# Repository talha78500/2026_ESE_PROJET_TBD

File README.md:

# 2026_ESE_PROJET_TBD

## Procédure de test de la carte

### Tests d'alimentation

La 1ère étape pour tester le pcb est de souder les solder bridges. Une fois les soudures faites, une alimentation de laboratoire est utilisée pour alimenter la carte. Pour ne pas endommager la carte en cas de court circuit, le courant de l'alimentation est limité à 100mA. On peut ensuite venir tester un à un les différents points de test de la carte. Les différents points de test sont relié au 5v, 3v3, sys et GND. Lors des des tests d'alimentation, des led temoigneront du fonctionnement : 

<div align="center">

</div>

| Test point alimenté | LED Temoin | LED allumée(s) en conséquence |Explication |
| :--- | :--- | :--- | :--- |
| 3v3 | Led rouge D1| X |X |
| 5v  | Led verte D2 | Led verte D2 orange D3 et rouge D4 | Le 5v alimente le régulateur 3v3 donc la led D2 s'allume. |
| SYS | Led rouge D4| X |X |

### Test du chargeur

Avant d'utiliser la batterie, les premiers essais du chargeur sont réalisés avec une alimentation 3v8 1A. Il faut programmer le chargeur via I2C: 
- Désactiver le timer interne (REG07, bits 5:4 = 00)
- Configurer la tension de sortie  boostée (REG0A)
- Couper la charge (REG03) (CHG_CONFIG = 0->Bit 4)
- Activer la sortie boostée (REG03) (OTG_CONFIG = 1 ->Bit 5)

Une fois tout cette partie validée, la batterie peut être branchée.

### Test du fuel gauge 

---

## Mise à jour OTA (PC → BLE → nRF52840 → UART → STM32G431)

### 1. Contexte et architecture

Le PCB ne donnant pas accès aux broches `NRST` et `BOOT0` de la STM32G431RBT6 depuis le nRF52840 (`nice!nano`), la reprogrammation passe exclusivement par la liaison UART reliant les deux microcontrôleurs :

| Signal | STM32G431RBT6 (`USART3`) | nRF52840 `nice!nano` (`uart0`) | Paramètres |
| :--- | :--- | :--- | :--- |
| TX → RX | `PC10` (`USART3_TX`) | `P0.08` (`UART_RX`, pull-up) | `115200` bauds, `8N1` |
| RX ← TX | `PC11` (`USART3_RX`) | `P0.06` (`UART_TX`) | Sans contrôle de flux |

Le nRF52840 ne disposant pas de contrôleur Wi-Fi intégré, la réception sans fil du firmware depuis le PC s'effectue en **Bluetooth Low Energy (BLE)** via une interface Web Bluetooth locale en glisser-déposer.

```text
PC (Chrome/Edge : stm32_ble_ota.html)
        │  BLE GATT ("Robot_STM32_OTA", paquets MTU jusqu'à 244 o)
        ▼
nRF52840 (Zephyr / NCS v2.9.3 : tampon RAM 112 Ko + contrôle CRC32)
        │  UART 115200 8N1 (P0.06 TX / P0.08 RX)
        ▼
STM32G431 (Bootloader permanent 0x08000000 → Flash App 0x08004000)
```

---

### 2. Cartographie mémoire STM32G431RBT6

La Flash interne (`128 Ko`, `64` pages de `2 Ko`, banque unique) et la SRAM (`32 Ko`) sont partitionnées ainsi :

| Zone | Plage d'adresses | Taille | Rôle |
| :--- | :--- | :--- | :--- |
| **Bootloader permanent** | `0x08000000` – `0x08003FFF` | `16 Ko` (pages 0..7) | Reçoit le firmware sur `USART3`, écrit la Flash App et saute vers l'application |
| **Application Robot** | `0x08004000` – `0x0801FFFF` | `112 Ko` (pages 8..63) | Firmware robot FreeRTOS (`SCB->VTOR = 0x08004000`) avec écoute OTA active |
| **SRAM applicative** | `0x20000000` – `0x20007FEF` | `32 Ko - 16 o` | Pile, heap et variables (`_estack = 0x20007FF0`) |
| **Mailbox OTA SRAM** | `0x20007FF0` – `0x20007FFF` | `16 octets` | Drapeau `0xB00710AD` posé avant `NVIC_SystemReset()` pour forcer l'entrée en bootloader |

---

### 3. Protocole série OTA et mécanisme de mise à jour

- **Format de trame (`Informatics/ota/ota_protocol.h`) :**
  `[0xAA, 0x55, CMD, LEN_LE (2 o), PAYLOAD (0..260 o), CRC32_LE (4 o)]` (CRC-32 IEEE 802.3).
  Réponses STM32 fixes sur `4` octets : `[0xAA, 0x55, RSP, ERR]` (`ACK=0x79`, `NACK=0x1F`, `READY=0x5A`, `REBOOTING=0x55`).
- **Auto-hébergement des mises à jour futures :**
  Chaque firmware applicatif initialise `ota_init(&huart3)` et appelle `ota_process()` dans la boucle FreeRTOS (`Core/Src/app_freertos.c`). Lorsqu'une trame `OTA_CMD_SYNC` (ou `"$$OTA$$"`, ou la commande shell `ota`) arrive :
  1. L'application coupe les moteurs (`motor_stop_all()`), répond `OTA_RSP_REBOOTING`, écrit `0xB00710AD` dans la mailbox SRAM et déclenche `NVIC_SystemReset()`.
  2. Le bootloader démarre, détecte la mailbox, efface `0` et répond `OTA_RSP_READY`. *(Au boot normal sans mailbox, il attend `350 ms` un `SYNC` éventuel avant de sauter vers l'app valide.)*
  3. **`OTA_CMD_BEGIN`** : transmet la taille totale et le CRC32 ; le bootloader efface uniquement les pages applicatives nécessaires (`>= page 8`).
  4. **`OTA_CMD_DATA`** : transfère le `.bin` par blocs de `256` octets max (écriture double-word `64 bits`, retry idempotent jusqu'à `3` tentatives).
  5. **`OTA_CMD_END`** : recalcule le CRC32 sur toute la zone écrite, vérifie le vecteur `MSP`/`Reset_Handler` à `0x08004000`, puis exécute `jump_to_app()`.
- **Cohabitation avec les `printf` :** `_write()` envoie aussi les sorties texte sur `USART3`. Le décodeur côté nRF52840 ignore les octets hors trame `[0xAA, 0x55, ...]` pendant l'OTA et relaie les lignes `[STM32] ...` sur la console USB de la `nice!nano` au repos.

---

### 4. Inventaire des fichiers ajoutés et modifiés

#### Côté STM32 & CMake (`Informatics/`)
- `ota/ota_protocol.h` : constantes, cartographie, CRC32 et format de trames partagés STM32 / nRF52840.
- `bootloader/boot_main.c` & `bootloader/STM32G431xx_BOOT.ld` : bootloader UART3 autonome (`16 Ko`, compilé en `-O2`).
- `app/ota.h` & `app/ota.c` : écoute `USART3` sous interruption, détection `SYNC`/`$$OTA$$`, arrêt moteurs et bascule vers le bootloader.
- `STM32G431xx_FLASH.ld` : décalage Flash de l'application à `0x08004000` (`112 Ko`) et réservation des `16` derniers octets de SRAM.
- `CMakeLists.txt` : ajout des sources OTA, génération automatique de `Informatics.bin` et de la cible `Informatics_Bootloader` (`Informatics_Bootloader.elf` / `.bin`).
- `Core/Src/main.c`, `Core/Src/app_freertos.c`, `Core/Src/stm32g4xx_it.c`, `Core/Src/stm32g4xx_hal_msp.c` : redirection `SCB->VTOR = OTA_APP_ADDR`, diffusion `printf` sur `USART2` + `USART3`, init/polling OTA et callback `USART3`.
- `bsp/uart_console.h`, `bsp/uart_console.c`, `app/shell.c` : routage des callbacks HAL secondaires vers `ota.c` et ajout de la commande shell `ota`.

#### Côté nRF52840 Zephyr (`Informatics/nrf52840/`)
- `app.overlay` : configuration Devicetree de `&uart0` (`stm32-uart`) à `115200 8N1` sur `P0.06` (TX) et `P0.08` (RX).
- `prj.conf` & `CMakeLists.txt` : activation UART par interruption, `ring_buf`, logs USB CDC ACM et stack BLE SoftDevice (`CONFIG_BT=y`, `CONFIG_BT_CTLR=y`, `CONFIG_BT_L2CAP_TX_MTU=247`).
- `../ota/nrf52840_stm32_ota.h` & `../ota/nrf52840_stm32_ota.c` : pilote portable maître OTA UART (`nrf_stm32_ota_flash()`).
- `src/stm32_ota_zephyr.h` & `src/stm32_ota_zephyr.c` : backend Zephyr (ISR UART, `ring_buf` 512 o, mutex OTA).
- `src/stm32_ble_ota.h` & `src/stm32_ble_ota.c` : service GATT BLE (`7b5a0001..0003-3c91-4d2e-9a4b-8f12c0e5d100`, périphérique `Robot_STM32_OTA`), réception en RAM (`112 Ko`), vérification CRC32 + en-tête STM32, et thread dédié de flashage UART avec notifications de progression.
- `src/stm32_fw_image.h` & `src/main.c` : point d'entrée Zephyr, option d'image embarquée pour test autonome, et relais des logs STM32.

#### Côté PC (`Informatics/ota/`)
- `stm32_ble_ota.html` : interface Web Bluetooth (glisser-déposer `.bin`, contrôle de l'adresse de reset `>= 0x08004000`, adaptation automatique au MTU BLE, barres de progression BLE et UART).
- `start_ble_ota_ui.bat` : lance un serveur HTTP local sur `http://127.0.0.1:8090/stm32_ble_ota.html` (requis par Chrome/Edge pour autoriser Web Bluetooth).

---

### 5. Procédure de déploiement et d'utilisation

1. **Première programmation du bootloader STM32 (1 seule fois via ST-Link) :**
   ```powershell
   & "C:\Program Files\STMicroelectronics\STM32Cube\STM32CubeProgrammer\bin\STM32_Programmer_CLI.exe" -c port=SWD -w Informatics\build\Debug\Informatics_Bootloader.bin 0x08000000 -v -rst
   ```
   *(En cas de flashage ultérieur d'une appli via ST-Link/CubeIDE, ne pas activer « Full chip erase » afin de conserver les 16 premiers Ko du bootloader.)*

2. **Programmation du nRF52840 (`nice!nano`) :**
   Double-appuyer sur Reset et copier `Informatics/nrf52840/build/zephyr/zephyr.uf2` sur le lecteur USB `NICENANO`.

3. **Mise à jour sans fil d'un nouveau firmware STM32 :**
   - Compiler le projet STM32 (`Informatics.bin` généré dans `Informatics/build/Debug/`).
   - Lancer `Informatics/ota/start_ble_ota_ui.bat` et ouvrir la page dans Chrome ou Edge.
   - Cliquer sur **Connecter au nRF52840** (`Robot_STM32_OTA`), glisser-déposer `Informatics.bin`, puis cliquer sur **Flasher la STM32**.

> **Important pour tout futur firmware STM32 :** chaque binaire destiné à l'OTA doit conserver le décalage Flash à `0x08004000`, positionner `SCB->VTOR = 0x08004000UL`, et inclure `ota_init(&huart3)` + `ota_process()` afin de pouvoir être mis à jour à son tour.

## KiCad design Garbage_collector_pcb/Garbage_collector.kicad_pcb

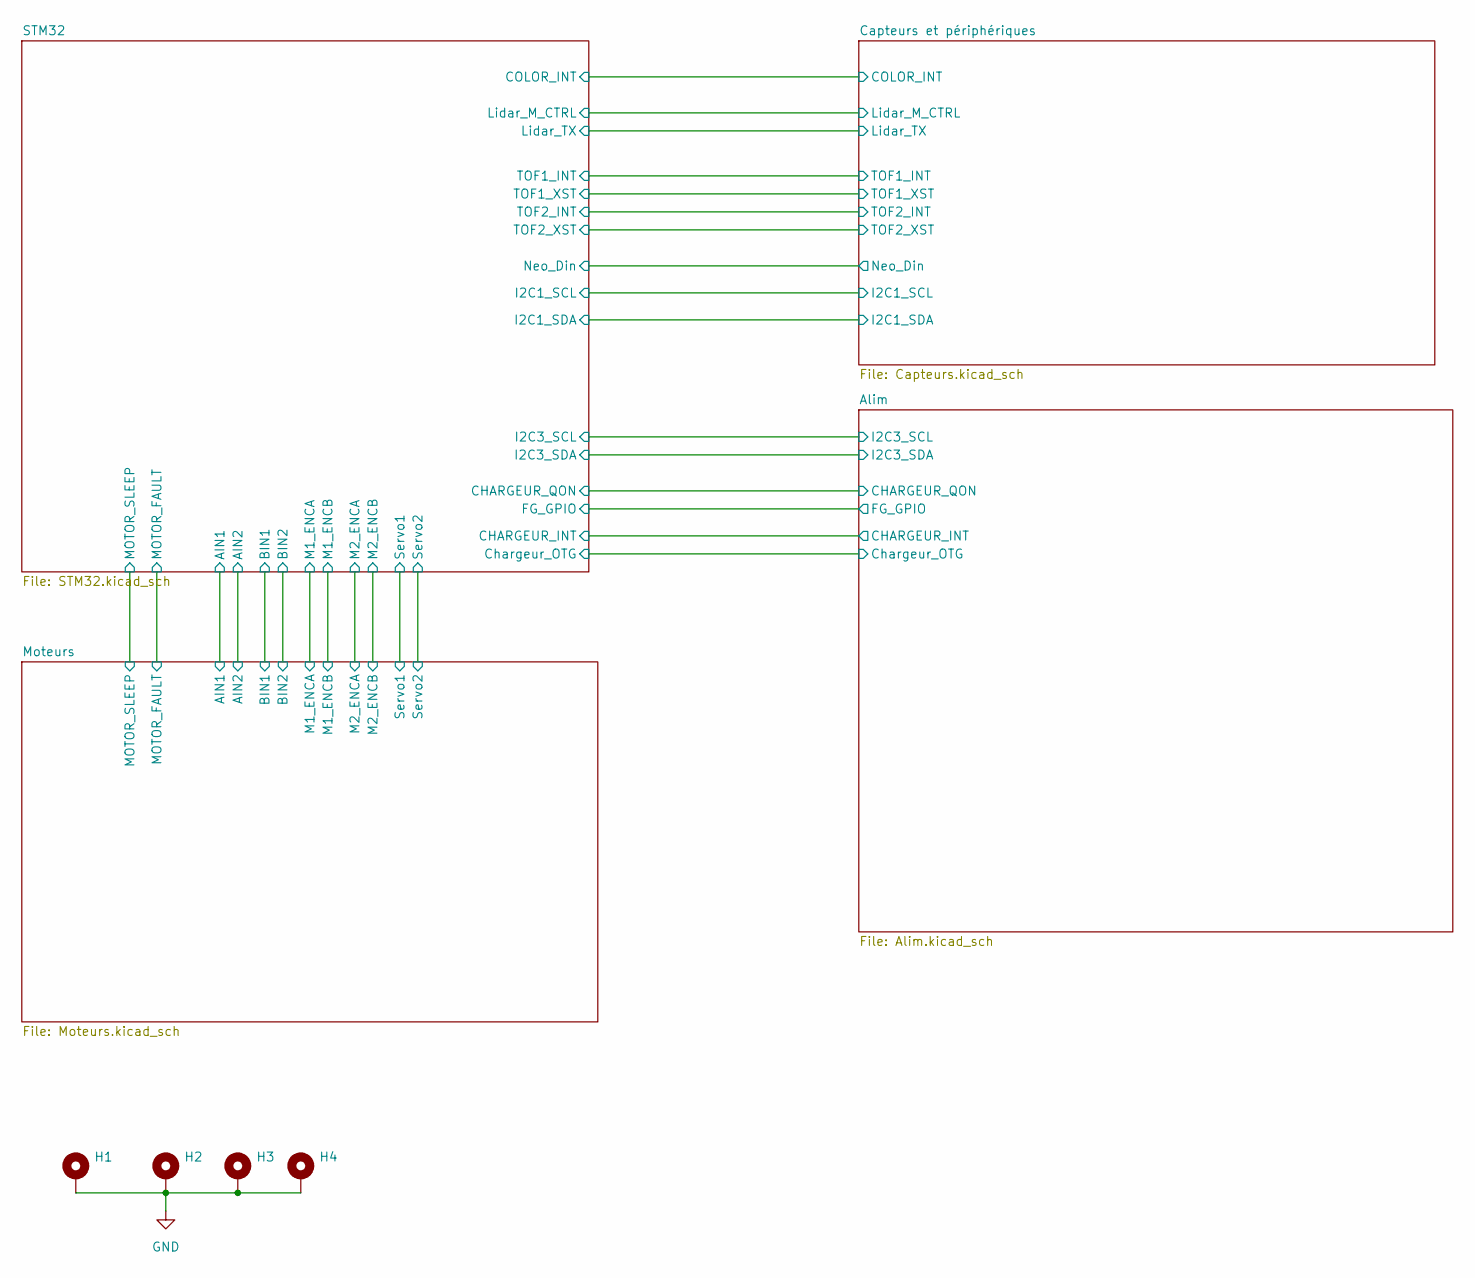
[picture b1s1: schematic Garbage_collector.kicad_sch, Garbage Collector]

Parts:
H1, H2, H3, H4: MountingHole_Pad; MountingHole_3.2mm_M3_ISO14580_Pad

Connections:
GND: H1.1 (1_1), H2.1 (1_1), H3.1 (1_1), H4.1 (1_1); also elsewhere on the board

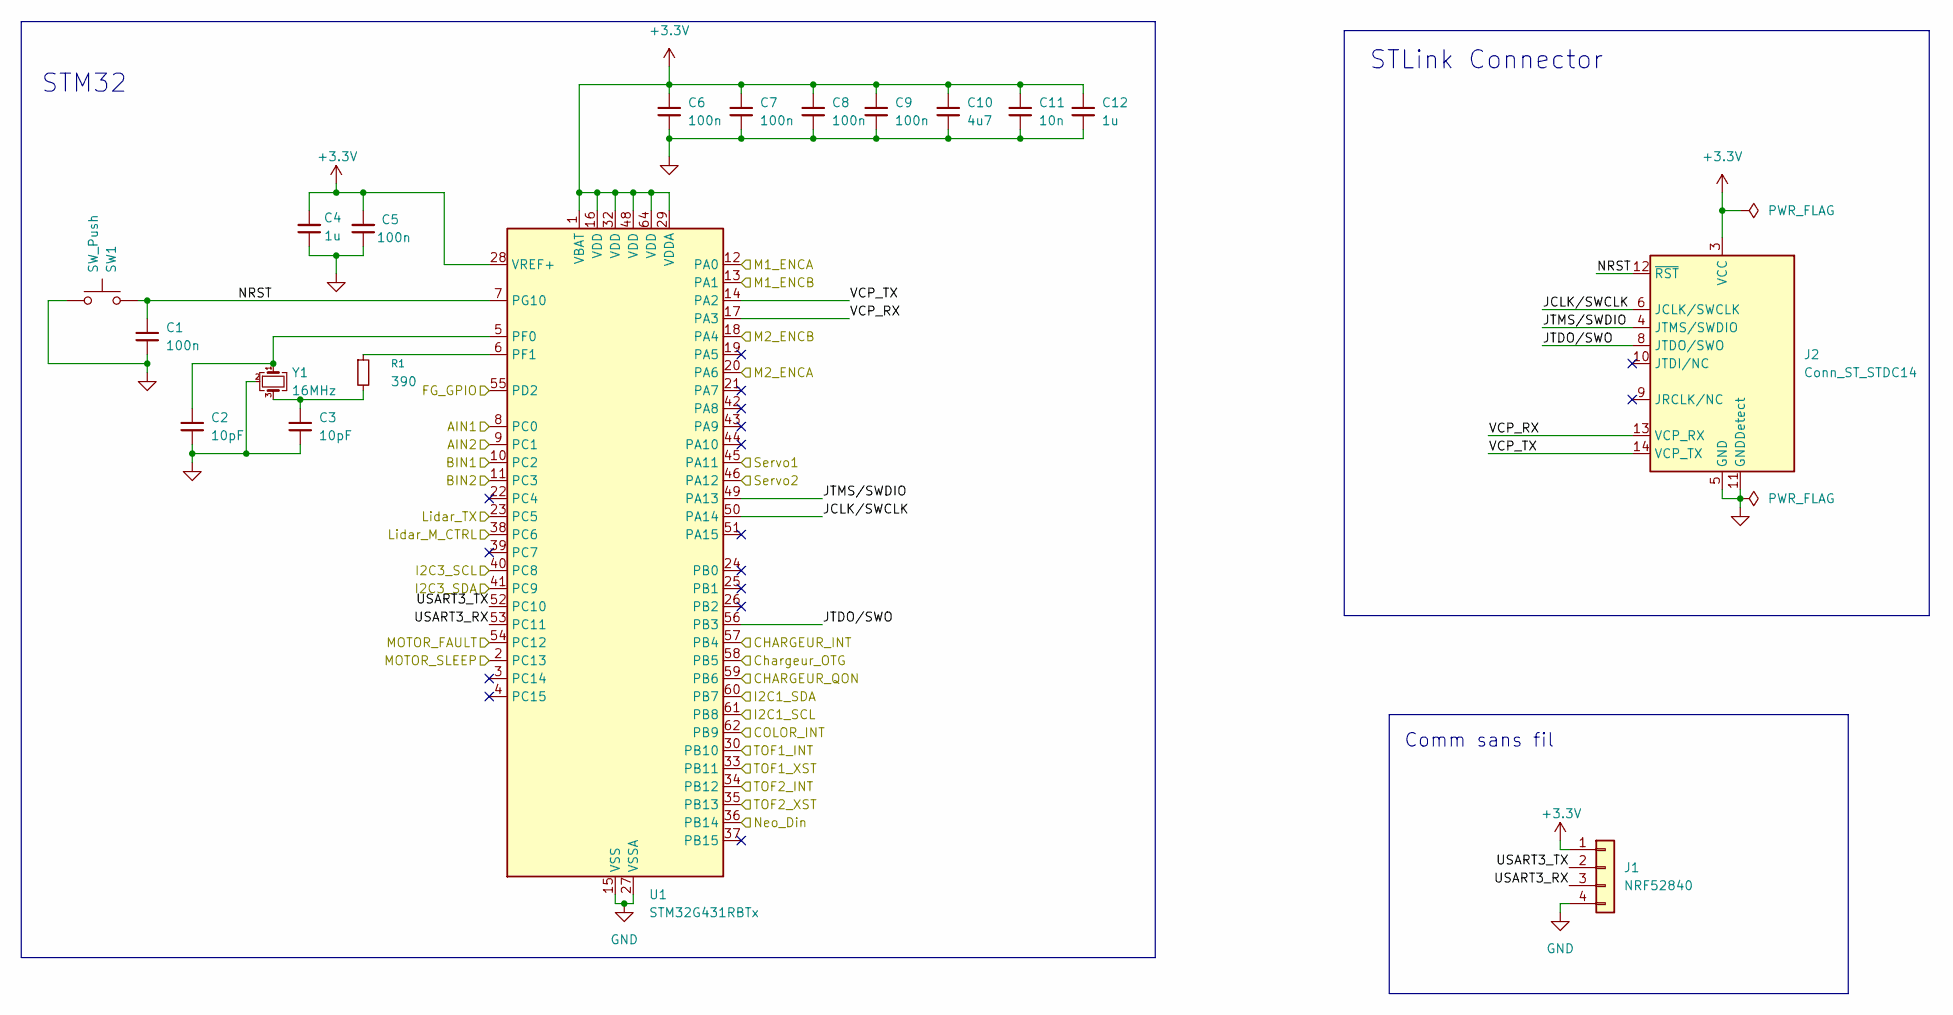
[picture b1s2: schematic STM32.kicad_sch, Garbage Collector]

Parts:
C1, C5, C6, C7, C8, C9: 100n; C_0402_1005Metric; JLCPCB Part # C1525
C2, C3: 10pF; C_0402_1005Metric; JLCPCB Part # C32949
C4, C12: 1u; C_0402_1005Metric; JLCPCB Part # C29266
C10: 4u7; C_0402_1005Metric; JLCPCB Part # C23733
C11: 10n; C_0402_1005Metric; JLCPCB Part # C15195
J1: NRF52840; JST_GH_BM04B-GHS-TBT_1x04-1MP_P1.25mm_Vertical; JLCPCB Part # C161692
J2: Conn_ST_STDC14; PinHeader_2x07_P1.27mm_Vertical_SMD; JLCPCB Part # C3975190
R1: 390; R_0402_1005Metric; JLCPCB Part # C22356179
SW1: SW_Push; SW_Push_1P1T_NO_CK_KMR2; JLCPCB Part # C72443
U1: STM32G431RBTx; LQFP-64_10x10mm_P0.5mm; JLCPCB Part # C431633
Y1: 16MHz; Crystal_SMD_EuroQuartz_MT-4Pin_3.2x2.5mm; JLCPCB Part # C13738

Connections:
+3.3V: C4.2, C5.2, C6.1, C7.1, C8.1, C9.1, C10.1, C11.1, C12.1, J1.1, J2.3 (VCC), U1.1 (VBAT), U1.16 (VDD), U1.28 (VREF+), U1.29 (VDDA), U1.32 (VDD), U1.48 (VDD), U1.64 (VDD); also elsewhere on the board
/Alim/CHARGEUR_INT: U1.57 (PB4); also elsewhere on the board
/Alim/CHARGEUR_QON: U1.59 (PB6); also elsewhere on the board
/Alim/Chargeur_OTG: U1.58 (PB5); also elsewhere on the board
/Alim/FG_GPIO: U1.55 (PD2); also elsewhere on the board
/Alim/I2C3_SCL: U1.40 (PC8); also elsewhere on the board
/Alim/I2C3_SDA: U1.41 (PC9); also elsewhere on the board
/Capteurs et périphériques/COLOR_INT: U1.62 (PB9); also elsewhere on the board
/Capteurs et périphériques/I2C1_SCL: U1.61 (PB8); also elsewhere on the board
/Capteurs et périphériques/I2C1_SDA: U1.60 (PB7); also elsewhere on the board
/Capteurs et périphériques/Lidar_M_CTRL: U1.38 (PC6); also elsewhere on the board
/Capteurs et périphériques/Lidar_TX: U1.23 (PC5); also elsewhere on the board
/Capteurs et périphériques/Neo_Din: U1.36 (PB14); also elsewhere on the board
/Capteurs et périphériques/TOF1_INT: U1.30 (PB10); also elsewhere on the board
/Capteurs et périphériques/TOF1_XST: U1.33 (PB11); also elsewhere on the board
/Capteurs et périphériques/TOF2_INT: U1.34 (PB12); also elsewhere on the board
/Capteurs et périphériques/TOF2_XST: U1.35 (PB13); also elsewhere on the board
/Moteurs/AIN1: U1.8 (PC0); also elsewhere on the board
/Moteurs/AIN2: U1.9 (PC1); also elsewhere on the board
/Moteurs/BIN1: U1.10 (PC2); also elsewhere on the board
/Moteurs/BIN2: U1.11 (PC3); also elsewhere on the board
/Moteurs/M1_ENCA: U1.12 (PA0); also elsewhere on the board
/Moteurs/M1_ENCB: U1.13 (PA1); also elsewhere on the board
/Moteurs/M2_ENCA: U1.20 (PA6); also elsewhere on the board
/Moteurs/M2_ENCB: U1.18 (PA4); also elsewhere on the board
/Moteurs/MOTOR_FAULT: U1.54 (PC12); also elsewhere on the board
/Moteurs/MOTOR_SLEEP: U1.2 (PC13); also elsewhere on the board
/Moteurs/Servo1: U1.45 (PA11); also elsewhere on the board
/Moteurs/Servo2: U1.46 (PA12); also elsewhere on the board
/STM32/JCLK/SWCLK: J2.6 (JCLK/SWCLK), U1.50 (PA14)
/STM32/JTDO/SWO: J2.8 (JTDO/SWO), U1.56 (PB3)
/STM32/JTMS/SWDIO: J2.4 (JTMS/SWDIO), U1.49 (PA13)
/STM32/NRST: C1.1, J2.12 (~RST), SW1.1, U1.7 (PG10)
/STM32/USART3_RX: J1.3, U1.53 (PC11)
/STM32/USART3_TX: J1.2, U1.52 (PC10)
/STM32/VCP_RX: J2.13 (VCP_RX), U1.17 (PA3)
/STM32/VCP_TX: J2.14 (VCP_TX), U1.14 (PA2)
GND: C1.2, C2.2, C3.2, C4.1, C5.1, C6.2, C7.2, C8.2, C9.2, C10.2, C11.2, C12.2, J1.4, J2.5 (GND), J2.7 (GND), J2.11 (GNDDetect), SW1.2, U1.15 (VSS), U1.27 (VSSA), U1.31 (VSS), U1.47 (VSS), U1.63 (VSS), Y1.2 (G), Y1.4 (G); also elsewhere on the board
unnamed: C3.1, R1.2, Y1.3
unnamed: C2.1, U1.5 (PF0), Y1.1
unnamed: R1.1, U1.6 (PF1)

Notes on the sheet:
Comm sans fil
STM32
STLink Connector

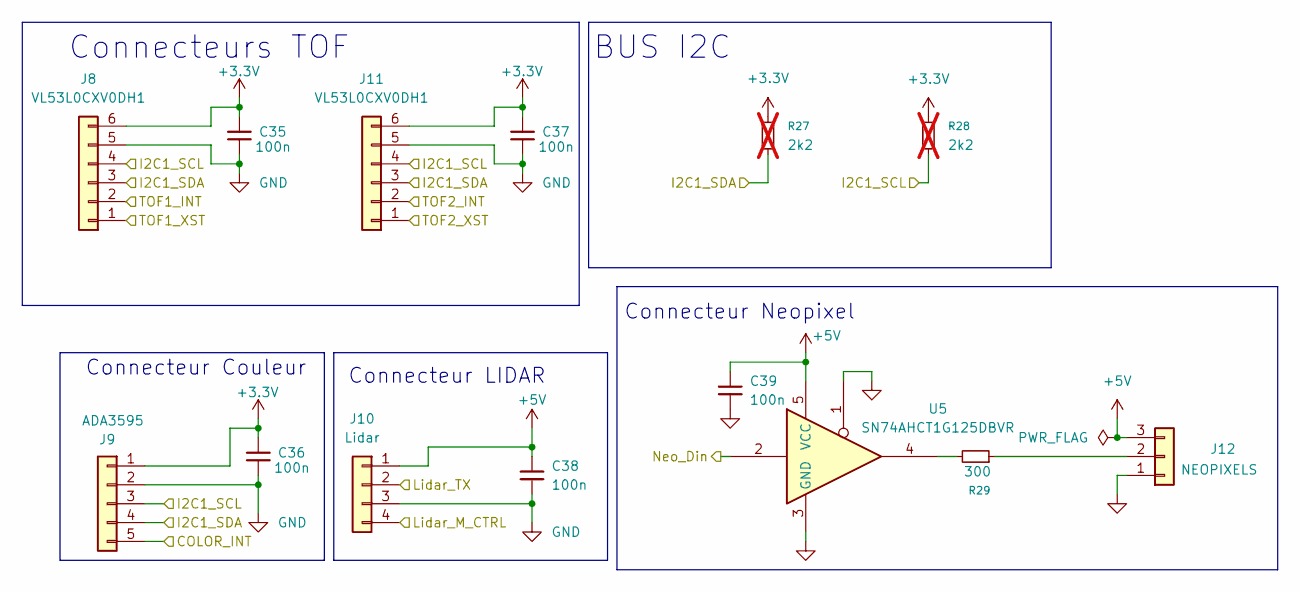
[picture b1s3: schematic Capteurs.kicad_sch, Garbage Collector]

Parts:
C35, C36, C37, C38, C39: 100n; C_0402_1005Metric; JLCPCB Part # C1525
J8, J11: VL53L0CXV0DH1; JST_GH_SM06B-GHS-TB_1x06-1MP_P1.25mm_Horizontal; JLCPCB Part # C225129
J9: ADA3595; JST_GH_BM05B-GHS-TBT_1x05-1MP_P1.25mm_Vertical; JLCPCB Part # C225128
J10: Lidar; JST_GH_BM04B-GHS-TBT_1x04-1MP_P1.25mm_Vertical; JLCPCB Part # C161692
J12: NEOPIXELS; JST_GH_SM03B-GHS-TB_1x03-1MP_P1.25mm_Horizontal; JLCPCB Part # C514175
R27, R28: 2k2; R_0402_1005Metric; JLCPCB Part # C25879; not fitted
R29: 300; R_0603_1608Metric; MPN 4D02WGJ0152TCE; JLCPCB Part # C23025
U5: SN74AHCT1G125DBVR; SOT-23-5; JLCPCB Part # C20617903

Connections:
+3.3V: C35.1, C36.1, C37.1, J8.6, J9.1, J11.6, R27.1, R28.1; also elsewhere on the board
+5V: C38.1, C39.1, J10.1, J12.3, U5.5 (VCC); also elsewhere on the board
/Capteurs et périphériques/COLOR_INT: J9.5; also elsewhere on the board
/Capteurs et périphériques/I2C1_SCL: J8.4, J9.3, J11.4, R28.2; also elsewhere on the board
/Capteurs et périphériques/I2C1_SDA: J8.3, J9.4, J11.3, R27.2; also elsewhere on the board
/Capteurs et périphériques/Lidar_M_CTRL: J10.4; also elsewhere on the board
/Capteurs et périphériques/Lidar_TX: J10.2; also elsewhere on the board
/Capteurs et périphériques/Neo_Din: U5.2; also elsewhere on the board
/Capteurs et périphériques/TOF1_INT: J8.2; also elsewhere on the board
/Capteurs et périphériques/TOF1_XST: J8.1; also elsewhere on the board
/Capteurs et périphériques/TOF2_INT: J11.2; also elsewhere on the board
/Capteurs et périphériques/TOF2_XST: J11.1; also elsewhere on the board
GND: C35.2, C36.2, C37.2, C38.2, C39.2, J8.5, J9.2, J10.3, J11.5, J12.1, U5.1, U5.3 (GND); also elsewhere on the board
unnamed: J12.2, R29.1
unnamed: R29.2, U5.4

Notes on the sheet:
Connecteurs TOF
Connecteur Neopixel
BUS I2C
Connecteur Couleur
Connecteur LIDAR

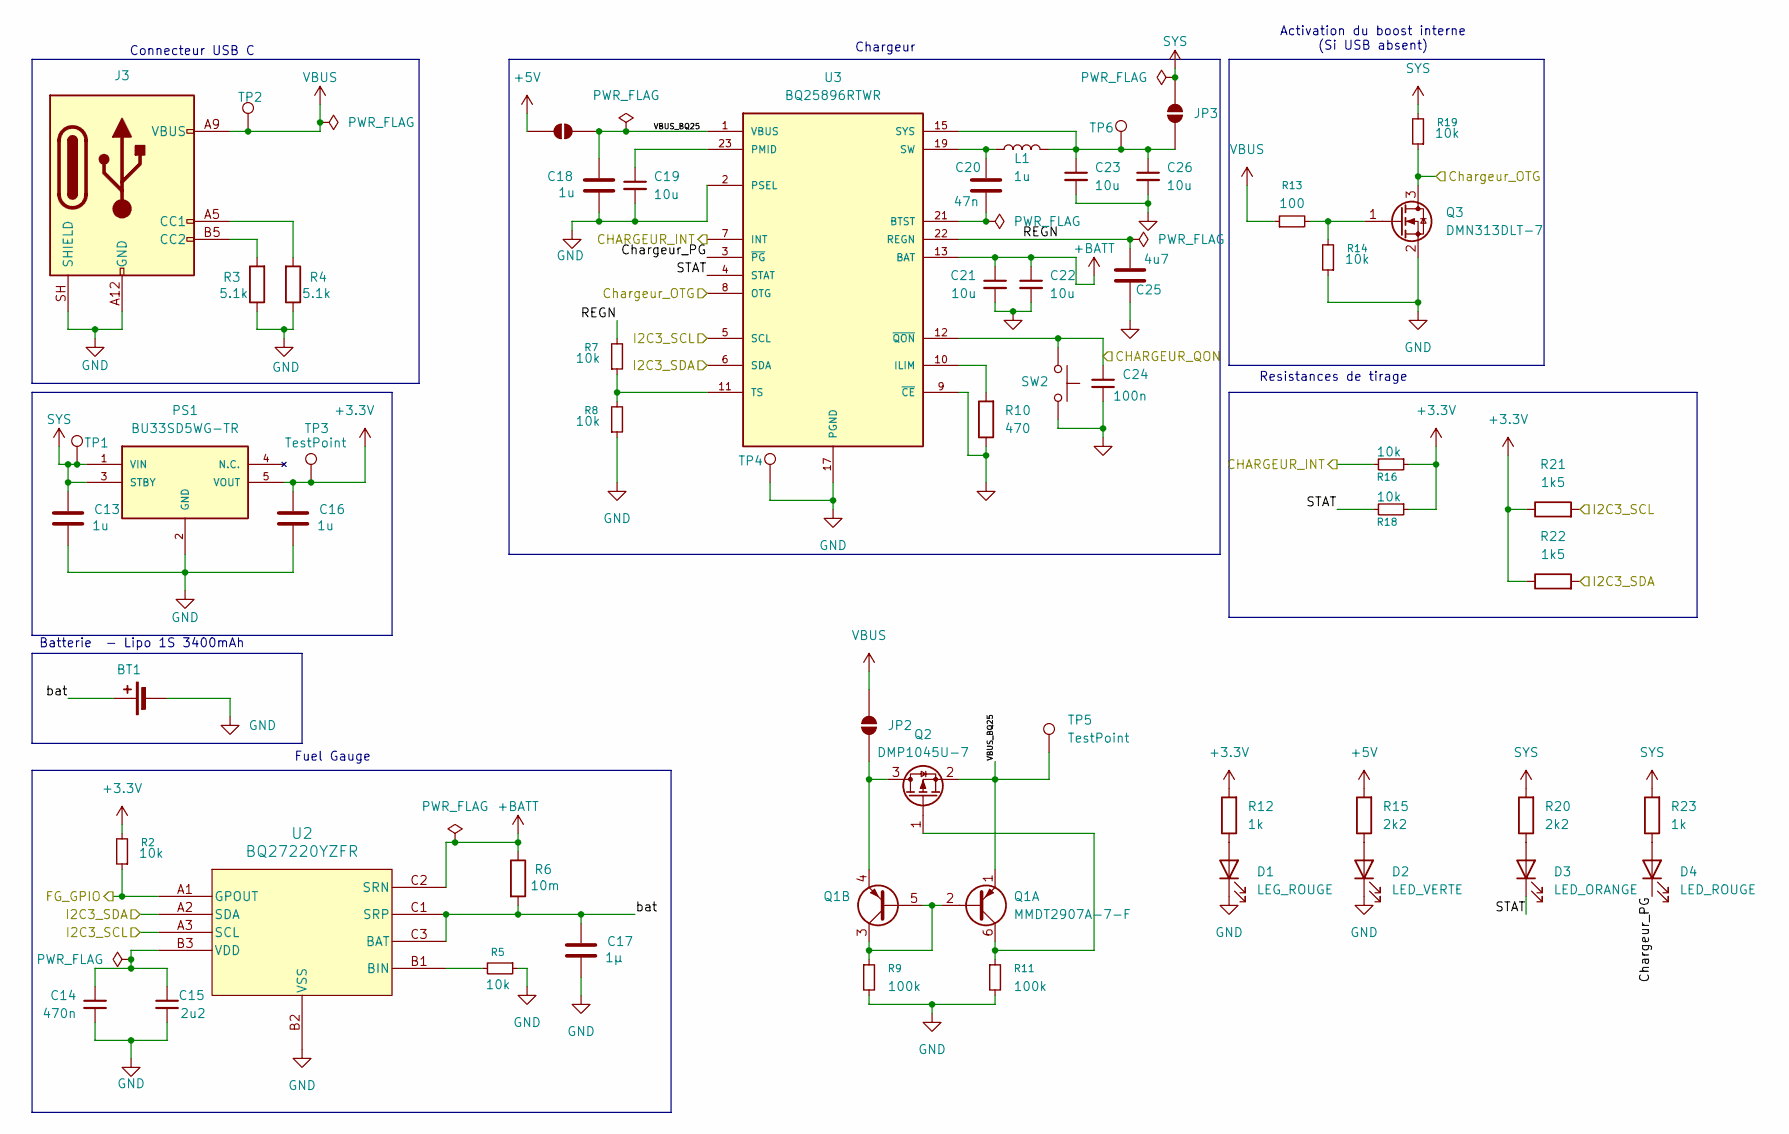
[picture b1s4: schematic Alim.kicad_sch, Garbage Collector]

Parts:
BT1: Battery_Cell; JST_GH_SM02B-GHS-TB_1x02-1MP_P1.25mm_Horizontal; JLCPCB Part # C54769875
C13, C16, C18: 1u; C_0402_1005Metric; JLCPCB Part # C29266
C14: 470n; C_0402_1005Metric; JLCPCB Part # C162162
C15: 2u2; C_0402_1005Metric; JLCPCB Part # C12530
C17: 1µ; C_0402_1005Metric; JLCPCB Part # C29266
C19, C21, C22, C23, C26: 10u; C_0402_1005Metric; JLCPCB Part # C15525
C20: 47n; C_0402_1005Metric; JLCPCB Part # C82219
C24: 100n; C_0402_1005Metric; JLCPCB Part # C1525
C25: 4u7; C_0402_1005Metric; JLCPCB Part # C23733
D1: LEG_ROUGE; LED_0603_1608Metric; JLCPCB Part# C2286
D2: LED_VERTE; LED_0603_1608Metric; JLCPCB Part# C99289
D3: LED_ORANGE; LED_0603_1608Metric; JLCPCB Part# C84269
D4: LED_ROUGE; LED_0603_1608Metric; JLCPCB Part# C2286
J3: USB_C_Receptacle_PowerOnly_6P; USB_C_Receptacle_GCT_USB4125-xx-x-0190_6P_TopMnt_Horizontal; JLCPCB Part # C963366
JP1, JP2, JP3: SolderJumper_2_Open; SolderJumper-2_P1.3mm_Open_TrianglePad1.0x1.5mm
L1: 1u; L_1008_2520Metric; JLCPCB Part # C167447
PS1: BU33SD5WG-TR; TSOP-5_1.65x3.05mm_P0.95mm; JLCPCB Part # C3750265
Q1: MMDT2907A-7-F; SOT-363_SC-70-6; JLCPCB Part # C460232
Q2: DMP1045U-7; SOT-23; JLCPCB Part # C177033
Q3: DMN313DLT-7; SOT-523; JLCPCB Part # C155524
R2, R5, R7, R8, R14, R16, R18, R19: 10k; R_0402_1005Metric; JLCPCB Part # C25744
R3, R4: 5.1k; R_0402_1005Metric; JLCPCB Part # C25905
R6: 10m; R_2512_6332Metric; JLCPCB Part # C105142
R9, R11: 100k; R_0402_1005Metric; JLCPCB Part # C25741
R10: 470; R_0402_1005Metric; JLCPCB Part # C25117
R12, R23: 1k; R_0402_1005Metric; JLCPCB Part# C11702
R13: 100; R_0402_1005Metric; JLCPCB Part # C25138
R15, R20: 2k2; R_0402_1005Metric; JLCPCB Part# C25879
R21, R22: 1k5; R_0402_1005Metric; JLCPCB Part # C25867
SW2: SW_Push; SW_Push_1P1T_NO_CK_KMR2; JLCPCB Part # C72443
TP1, TP2, TP3, TP4, TP5, TP6: TestPoint; TestPoint_Pad_D2.0mm
U2: BQ27220YZFR; Texas_DSBGA-9_1.62x1.58mm_Layout3x3_P0.5mm; JLCPCB Part # C528617
U3: BQ25896RTWR; Texas_RTW_WQFN-24-1EP_4x4mm_P0.5mm_EP2.7x2.7mm; JLCPCB Part # C181475

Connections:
+3.3V: C16.2, PS1.5 (VOUT), R2.2, R12.2, R16.1, R18.1, R21.1, R22.1, TP3.1 (1_1); also elsewhere on the board
+5V: JP1.1 (A), R15.2; also elsewhere on the board
+BATT: C21.1, C22.1, R6.1, U2.C2 (SRN), U3.13 (BAT), U3.14 (BAT)
/Alim/CHARGEUR_INT: R16.2, U3.7 (INT); also elsewhere on the board
/Alim/CHARGEUR_QON: C24.2, SW2.1, U3.12 (~QON); also elsewhere on the board
/Alim/Chargeur_OTG: Q3.3 (D), R19.1, U3.8 (OTG); also elsewhere on the board
/Alim/Chargeur_PG: D4.1 (K), U3.3 (~PG)
/Alim/FG_GPIO: R2.1, U2.A1 (GPOUT); also elsewhere on the board
/Alim/I2C3_SCL: R21.2, U2.A3 (SCL), U3.5 (SCL); also elsewhere on the board
/Alim/I2C3_SDA: R22.2, U2.A2 (SDA), U3.6 (SDA); also elsewhere on the board
/Alim/REGN: C25.2, R7.2, U3.22 (REGN)
/Alim/STAT: D3.1 (K), R18.2, U3.4 (STAT)
/Alim/VBUS_BQ25: C18.2, JP1.2 (B), Q1.1 (E1), Q2.2 (S), TP5.1 (1_1), U3.1 (VBUS)
/Alim/bat: BT1.1 (+), C17.2, R6.2, U2.C1 (SRP), U2.C3 (BAT)
GND: BT1.2 (-), C13.1, C14.2, C15.2, C16.1, C17.1, C18.1, C19.2, C21.2, C22.2, C23.2, C24.1, C25.1, C26.2, D1.1 (K), D2.1 (K), J3.A12 (GND), J3.B12 (GND), J3.SH (SHIELD), PS1.2 (GND), Q3.2 (S), R3.1, R4.1, R5.1, R8.1, R9.2, R10.1, R11.2, R14.1, SW2.2, TP4.1 (1_1), U2.B2 (VSS), U3.2 (PSEL), U3.9 (~CE), U3.17 (PGND), U3.18 (PGND), U3.25 (EXP); also elsewhere on the board
unnamed: C20.2, L1.2, U3.19 (SW), U3.20 (SW)
unnamed: D1.2 (A), R12.1
unnamed: D2.2 (A), R15.1
unnamed: D3.2 (A), R20.1
unnamed: D4.2 (A), R23.1
unnamed: J3.A5 (CC1), R4.2
unnamed: J3.B5 (CC2), R3.2
unnamed: JP2.1 (A), Q1.4 (E2), Q2.3 (D)
unnamed: C23.1, C26.1, JP3.1 (A), L1.1, TP6.1 (1_1), U3.15 (SYS), U3.16 (SYS)
unnamed: Q1.2 (B1), Q1.3 (C2), Q1.5 (B2), R9.1
unnamed: Q1.6 (C1), Q2.1 (G), R11.1
unnamed: Q3.1 (G), R13.2, R14.2
unnamed: R5.2, U2.B1 (BIN)
unnamed: C14.1, C15.1, U2.B3 (VDD)
unnamed: C20.1, U3.21 (BTST)
unnamed: R10.2, U3.10 (ILIM)
unnamed: C19.1, U3.23 (PMID)
unnamed: R7.1, R8.2, U3.11 (TS)
SYS: C13.2, JP3.2 (B), PS1.1 (VIN), PS1.3 (STBY), R19.2, R20.2, R23.2, TP1.1 (1_1)
VBUS: J3.A9 (VBUS), J3.B9 (VBUS), JP2.2 (B), R13.1, TP2.1 (1_1)

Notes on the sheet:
Batterie - Lipo 1S 3400mAh
Fuel Gauge
Chargeur
Resistances de tirage
Connecteur USB C
Activation du boost interne (Si USB absent)

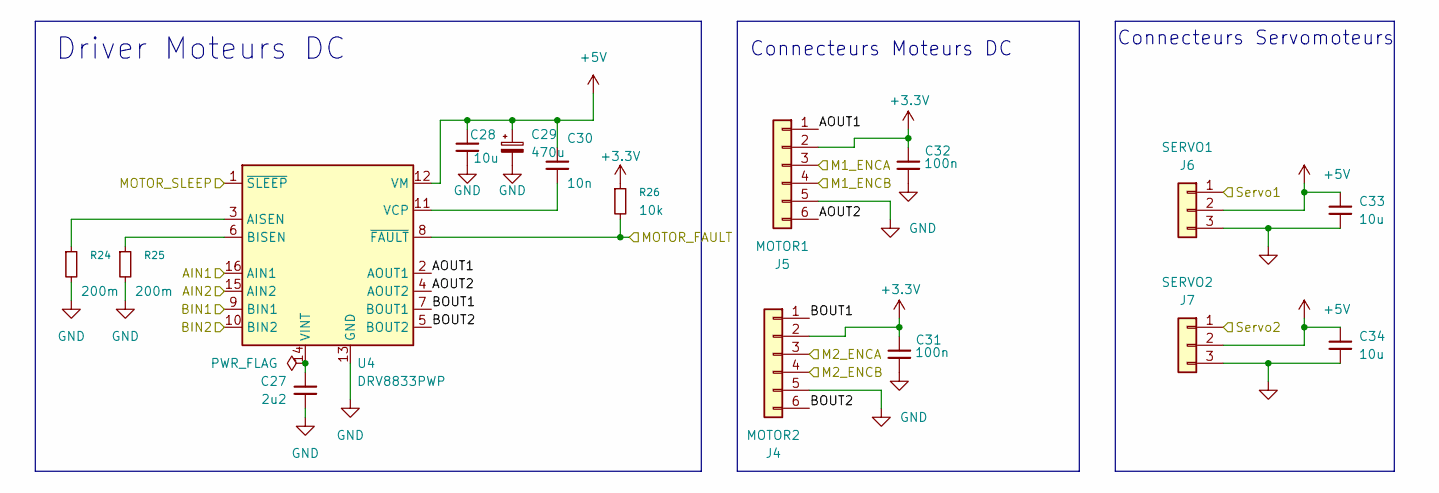
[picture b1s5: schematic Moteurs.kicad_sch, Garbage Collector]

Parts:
C27: 2u2; C_0402_1005Metric; JLCPCB Part # C12530
C28, C33, C34: 10u; C_0402_1005Metric; JLCPCB Part # C15525
C29: 470u; CP_Elec_10x10.5; JLCPCB Part # C96180
C30: 10n; C_0603_1608Metric; JLCPCB Part # C76614
C31, C32: 100n; C_0402_1005Metric; JLCPCB Part # C1525
J4: MOTOR2; JST_GH_SM06B-GHS-TB_1x06-1MP_P1.25mm_Horizontal; JLCPCB Part # C225129
J5: MOTOR1; JST_GH_SM06B-GHS-TB_1x06-1MP_P1.25mm_Horizontal; JLCPCB Part # C225129
J6: SERVO1; JST_GH_SM03B-GHS-TB_1x03-1MP_P1.25mm_Horizontal; JLCPCB Part # C514175
J7: SERVO2; JST_GH_SM03B-GHS-TB_1x03-1MP_P1.25mm_Horizontal; JLCPCB Part # C514175
R24, R25: 200m; R_0805_2012Metric; JLCPCB Part # C171371
R26: 10k; R_0402_1005Metric; JLCPCB Part # C25744
U4: DRV8833PWP; HTSSOP-16-1EP_4.4x5mm_P0.65mm_EP3.4x5mm_Mask2.46x2.31mm_The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; JLCPCB Part # C50506

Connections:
+3.3V: C31.1, C32.1, J4.2, J5.2, R26.1; also elsewhere on the board
+5V: C28.1, C29.1, C30.1, C33.1, C34.1, J6.2, J7.2, U4.12 (VM); also elsewhere on the board
/Moteurs/AIN1: U4.16 (AIN1); also elsewhere on the board
/Moteurs/AIN2: U4.15 (AIN2); also elsewhere on the board
/Moteurs/AOUT1: J5.1, U4.2 (AOUT1)
/Moteurs/AOUT2: J5.6, U4.4 (AOUT2)
/Moteurs/BIN1: U4.9 (BIN1); also elsewhere on the board
/Moteurs/BIN2: U4.10 (BIN2); also elsewhere on the board
/Moteurs/BOUT1: J4.1, U4.7 (BOUT1)
/Moteurs/BOUT2: J4.6, U4.5 (BOUT2)
/Moteurs/M1_ENCA: J5.3; also elsewhere on the board
/Moteurs/M1_ENCB: J5.4; also elsewhere on the board
/Moteurs/M2_ENCA: J4.3; also elsewhere on the board
/Moteurs/M2_ENCB: J4.4; also elsewhere on the board
/Moteurs/MOTOR_FAULT: R26.2, U4.8 (~FAULT); also elsewhere on the board
/Moteurs/MOTOR_SLEEP: U4.1 (~SLEEP); also elsewhere on the board
/Moteurs/Servo1: J6.1; also elsewhere on the board
/Moteurs/Servo2: J7.1; also elsewhere on the board
GND: C27.2, C28.2, C29.2, C31.2, C32.2, C33.2, C34.2, J4.5, J5.5, J6.3, J7.3, R24.2, R25.2, U4.13 (GND), U4.17 (GND); also elsewhere on the board
unnamed: R24.1, U4.3 (AISEN)
unnamed: R25.1, U4.6 (BISEN)
unnamed: C30.2, U4.11 (VCP)
unnamed: C27.1, U4.14 (VINT)

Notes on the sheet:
Driver Moteurs DC
Connecteurs Moteurs DC
Connecteurs Servomoteurs

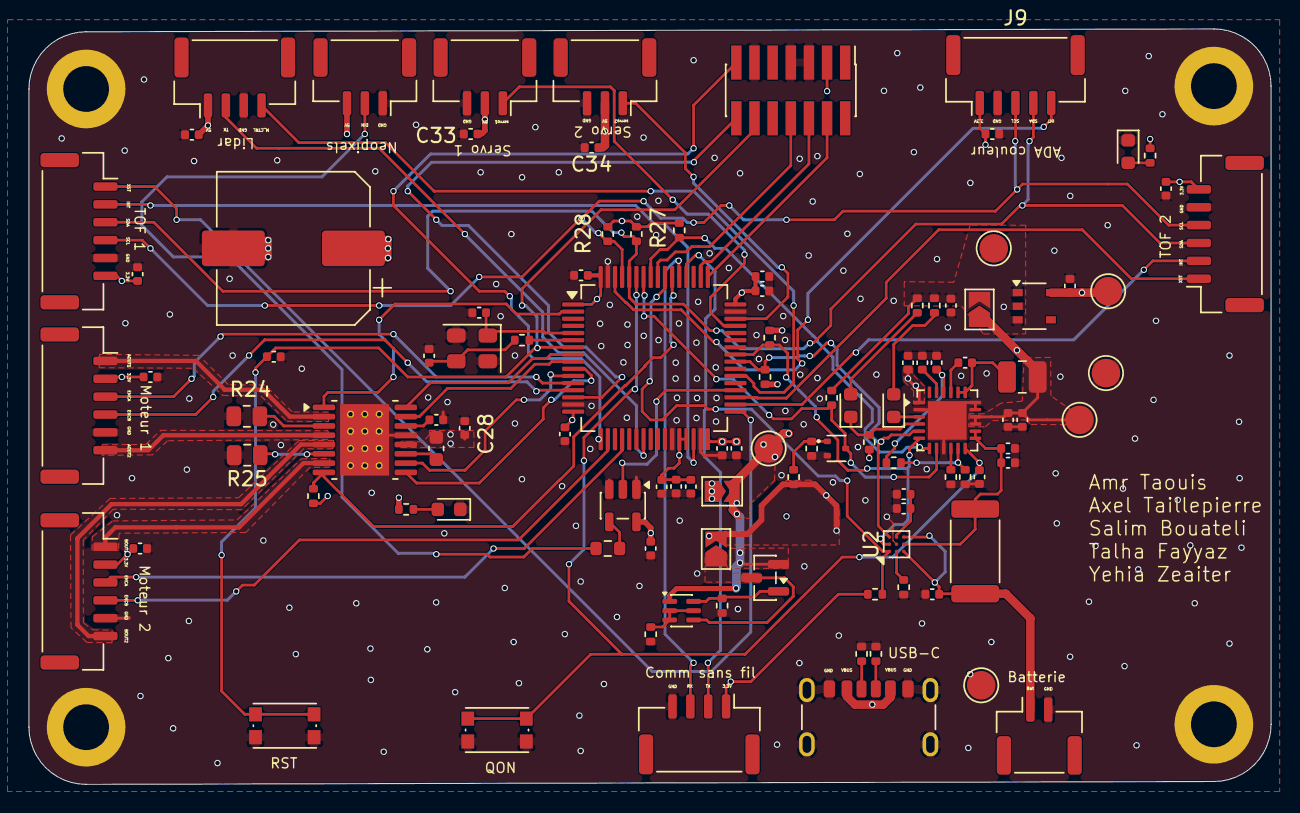
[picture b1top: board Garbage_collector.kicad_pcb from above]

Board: 4 copper layers, 86.9 x 52.9 mm, 110 parts (0 on the bottom side), 78 nets.

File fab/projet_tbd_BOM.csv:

"Designator ","Comment","Footprint","JLCPCB Part #"
"BT1","Battery_Cell","Connector_JST:JST_GH_SM02B-GHS-TB_1x02-1MP_P1.25mm_Horizontal","C54769875"
"C1,C5,C6,C7,C8,C9,C24,C31,C32,C35,C36,C37,C38,C39","100n","Capacitor_SMD:C_0402_1005Metric","C1525"
"C2,C3","10pF","Capacitor_SMD:C_0402_1005Metric","C32949"
"C4,C12,C13,C16,C18","1u","Capacitor_SMD:C_0402_1005Metric","C29266"
"C10,C25","4u7","Capacitor_SMD:C_0402_1005Metric","C23733"
"C11","10n","Capacitor_SMD:C_0402_1005Metric","C15195"
"C14","470n","Capacitor_SMD:C_0402_1005Metric","C162162"
"C15,C27","2u2","Capacitor_SMD:C_0402_1005Metric","C12530"
"C17","1µ","Capacitor_SMD:C_0402_1005Metric","C29266"
"C19,C21,C22,C23,C26,C28,C33,C34","10u","Capacitor_SMD:C_0402_1005Metric","C15525"
"C20","47n","Capacitor_SMD:C_0402_1005Metric","C82219"
"C29","470u","Capacitor_SMD:CP_Elec_10x10.5","C96180"
"C30","10n","Capacitor_SMD:C_0603_1608Metric","C76614"
"D1","LEG_ROUGE","LED_SMD:LED_0603_1608Metric","C2286"
"D2","LED_VERTE","LED_SMD:LED_0603_1608Metric","C99289"
"D3","LED_ORANGE","LED_SMD:LED_0603_1608Metric","C84269"
"D4","LED_ROUGE","LED_SMD:LED_0603_1608Metric","C2286"
"J1","NRF52840","Connector_JST:JST_GH_BM04B-GHS-TBT_1x04-1MP_P1.25mm_Vertical","C161692"
"J2","Conn_ST_STDC14","Connector_PinHeader_1.27mm:PinHeader_2x07_P1.27mm_Vertical_SMD","C3975190"
"J3","USB_C_Receptacle_PowerOnly_6P","Connector_USB:USB_C_Receptacle_GCT_USB4125-xx-x-0190_6P_TopMnt_Horizontal","C963366"
"J4","MOTOR2","Connector_JST:JST_GH_SM06B-GHS-TB_1x06-1MP_P1.25mm_Horizontal","C225129"
"J5","MOTOR1","Connector_JST:JST_GH_SM06B-GHS-TB_1x06-1MP_P1.25mm_Horizontal","C225129"
"J6","SERVO1","Connector_JST:JST_GH_SM03B-GHS-TB_1x03-1MP_P1.25mm_Horizontal","C514175"
"J7","SERVO2","Connector_JST:JST_GH_SM03B-GHS-TB_1x03-1MP_P1.25mm_Horizontal","C514175"
"J8,J11","VL53L0CXV0DH1","Connector_JST:JST_GH_SM06B-GHS-TB_1x06-1MP_P1.25mm_Horizontal","C225129"
"J9","ADA3595","Connector_JST:JST_GH_BM05B-GHS-TBT_1x05-1MP_P1.25mm_Vertical","C225128"
"J10","Lidar","Connector_JST:JST_GH_BM04B-GHS-TBT_1x04-1MP_P1.25mm_Vertical","C161692"
"J12","NEOPIXELS","Connector_JST:JST_GH_SM03B-GHS-TB_1x03-1MP_P1.25mm_Horizontal","C514175"
"L1","1u","Inductor_SMD:L_1008_2520Metric","C167447"
"PS1","BU33SD5WG-TR","Package_SO:TSOP-5_1.65x3.05mm_P0.95mm","C3750265"
"Q1","MMDT2907A-7-F","Package_TO_SOT_SMD:SOT-363_SC-70-6","C460232"
"Q2","DMP1045U-7","Package_TO_SOT_SMD:SOT-23","C177033"
"Q3","DMN313DLT-7","Package_TO_SOT_SMD:SOT-523","C155524"
"R1","390","Resistor_SMD:R_0402_1005Metric","C22356179"
"R2,R5,R7,R8,R14,R16,R18,R19,R26","10k","Resistor_SMD:R_0402_1005Metric","C25744"
"R3,R4","5.1k","Resistor_SMD:R_0402_1005Metric","C25905"
"R6","10m","Resistor_SMD:R_2512_6332Metric","C105142"
"R9,R11","100k","Resistor_SMD:R_0402_1005Metric","C25741"
"R10","470","Resistor_SMD:R_0402_1005Metric","C25117"
"R12,R23","1k","Resistor_SMD:R_0402_1005Metric","C11702"
"R13","100","Resistor_SMD:R_0402_1005Metric","C25138"
"R15,R20","2k2","Resistor_SMD:R_0402_1005Metric","C25879"
"R21,R22","1k5","Resistor_SMD:R_0402_1005Metric","C25867"
"R24,R25","200m","Resistor_SMD:R_0805_2012Metric","C171371"
"R29","300","Resistor_SMD:R_0603_1608Metric"," C23025"
"SW1,SW2","SW_Push","Button_Switch_SMD:SW_Push_1P1T_NO_CK_KMR2","C72443"
"U1","STM32G431RBTx","Package_QFP:LQFP-64_10x10mm_P0.5mm","C431633"
"U2","BQ27220YZFR","Package_BGA:Texas_DSBGA-9_1.62x1.58mm_Layout3x3_P0.5mm","C528617"
"U3","BQ25896RTWR","Package_DFN_QFN:Texas_RTW_WQFN-24-1EP_4x4mm_P0.5mm_EP2.7x2.7mm","C181475"
"U4","DRV8833PWP","Package_SO:HTSSOP-16-1EP_4.4x5mm_P0.65mm_EP3.4x5mm_Mask2.46x2.31mm_ThermalVias","C50506"
"U5","SN74AHCT1G125DBVR","Package_TO_SOT_SMD:SOT-23-5","C20617903"
"Y1","16MHz","Crystal:Crystal_SMD_EuroQuartz_MT-4Pin_3.2x2.5mm","C13738"

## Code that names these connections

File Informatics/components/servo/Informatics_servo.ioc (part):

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Mcu.Name=STM32G431R(6-8-B)Tx
Mcu.Package=LQFP64
Mcu.UserName=STM32G431RBTx
PA0.GPIOParameters=GPIO_Label
PA0.GPIO_Label=M1_ENCA
PA0.Signal=S_TIM2_CH1
PA1.GPIOParameters=GPIO_Label
PA1.GPIO_Label=M1_ENCB
PA1.Signal=S_TIM2_CH2
PA11.GPIOParameters=GPIO_Label
PA11.GPIO_Label=SERVO1
PA11.Signal=S_TIM4_CH1
PA12.GPIOParameters=GPIO_Label
PA12.GPIO_Label=SERVO2
PA12.Signal=S_TIM4_CH2
PA13.Mode=Trace_Asynchronous_SW
PA13.Signal=SYS_JTMS-SWDIO
PA14.Mode=Trace_Asynchronous_SW
PA14.Signal=SYS_JTCK-SWCLK
PA2.GPIOParameters=GPIO_Label
PA2.GPIO_Label=VCP_TX
PA2.Mode=Asynchronous
PA2.Signal=USART2_TX
PA3.GPIOParameters=GPIO_Label
PA3.GPIO_Label=VCP_RX
PA3.Mode=Asynchronous
PA3.Signal=USART2_RX
PA4.GPIOParameters=GPIO_Label
PA4.GPIO_Label=M2_ENCA
PA4.Signal=S_TIM3_CH2
PA6.GPIOParameters=GPIO_Label
PA6.GPIO_Label=M2_ENCB
PA6.Signal=S_TIM3_CH1
PB10.GPIOParameters=GPIO_Label
PB10.GPIO_Label=TOF1_INT
PB10.Signal=GPXTI10
PB11.GPIOParameters=GPIO_Label
PB11.GPIO_Label=TOF1_XST
PB11.Signal=GPIO_Output
PB12.GPIOParameters=GPIO_Label
PB12.GPIO_Label=TOF2_INT
PB12.Signal=GPXTI12
PB13.GPIOParameters=GPIO_Label
PB13.GPIO_Label=TOF2_XST
PB13.Signal=GPIO_Output
PB14.GPIOParameters=GPIO_Label
PB14.GPIO_Label=NEOPIXEL_DATA
PB14.Signal=S_TIM15_CH1
PB3.Mode=Trace_Asynchronous_SW
PB3.Signal=SYS_JTDO-SWO
PB4.GPIOParameters=GPIO_Label
PB4.GPIO_Label=CHARGEUR_INT
PB4.Signal=GPXTI4
PB5.GPIOParameters=GPIO_Label
PB5.GPIO_Label=CHARGEUR_PG
PB5.Signal=GPXTI5
PB6.GPIOParameters=GPIO_Label
PB6.GPIO_Label=CHARGEUR_QON
PB6.Signal=GPXTI6
PB7.Mode=I2C
PB7.Signal=I2C1_SDA
PB8-BOOT0.Mode=I2C
PB8-BOOT0.Signal=I2C1_SCL
PB9.GPIOParameters=GPIO_Label
PB9.GPIO_Label=COLOR_INT
PB9.Signal=GPXTI9
PC0.GPIOParameters=GPIO_Label
PC0.GPIO_Label=AIN1
PC0.Signal=S_TIM1_CH1
PC1.GPIOParameters=GPIO_Label
PC1.GPIO_Label=AIN2
PC1.Signal=S_TIM1_CH2
PC10.Mode=Asynchronous
PC10.Signal=USART3_TX
PC11.Mode=Asynchronous
PC11.Signal=USART3_RX
PC13.GPIOParameters=GPIO_Label
PC13.GPIO_Label=MOTOR_SLEEP
PC13.Signal=GPIO_Output
PC2.GPIOParameters=GPIO_Label
PC2.GPIO_Label=BIN1
PC2.Signal=S_TIM1_CH3
PC3.GPIOParameters=GPIO_Label
PC3.GPIO_Label=BIN2
PC3.Signal=S_TIM1_CH4
PC4.GPIOParameters=GPIO_Label
PC4.GPIO_Label=USART1_UNUSED
PC4.Mode=Asynchronous
PC4.Signal=USART1_TX
PC5.GPIOParameters=GPIO_Label
PC5.GPIO_Label=LIDAR_RX
PC5.Mode=Asynchronous
PC5.Signal=USART1_RX
PC6.GPIOParameters=GPIO_Label
PC6.GPIO_Label=LIDAR_CTRL
PC6.Signal=S_TIM8_CH1
PC8.Mode=I2C
PC8.Signal=I2C3_SCL
PC9.Mode=I2C
PC9.Signal=I2C3_SDA
PD2.GPIOParameters=GPIO_Label
PD2.GPIO_Label=FG_GPIO
PD2.Signal=GPXTI2
PF0-OSC_IN.Mode=HSE-External-Oscillator
PF0-OSC_IN.Signal=RCC_OSC_IN
PF1-OSC_OUT.Mode=HSE-External-Oscillator
PF1-OSC_OUT.Signal=RCC_OSC_OUT
RCC.HSE_VALUE=16000000
RCC.SYSCLKFreq_VALUE=170000000
RCC.SYSCLKSource=RCC_SYSCLKSOURCE_PLLCLK
board=custom
